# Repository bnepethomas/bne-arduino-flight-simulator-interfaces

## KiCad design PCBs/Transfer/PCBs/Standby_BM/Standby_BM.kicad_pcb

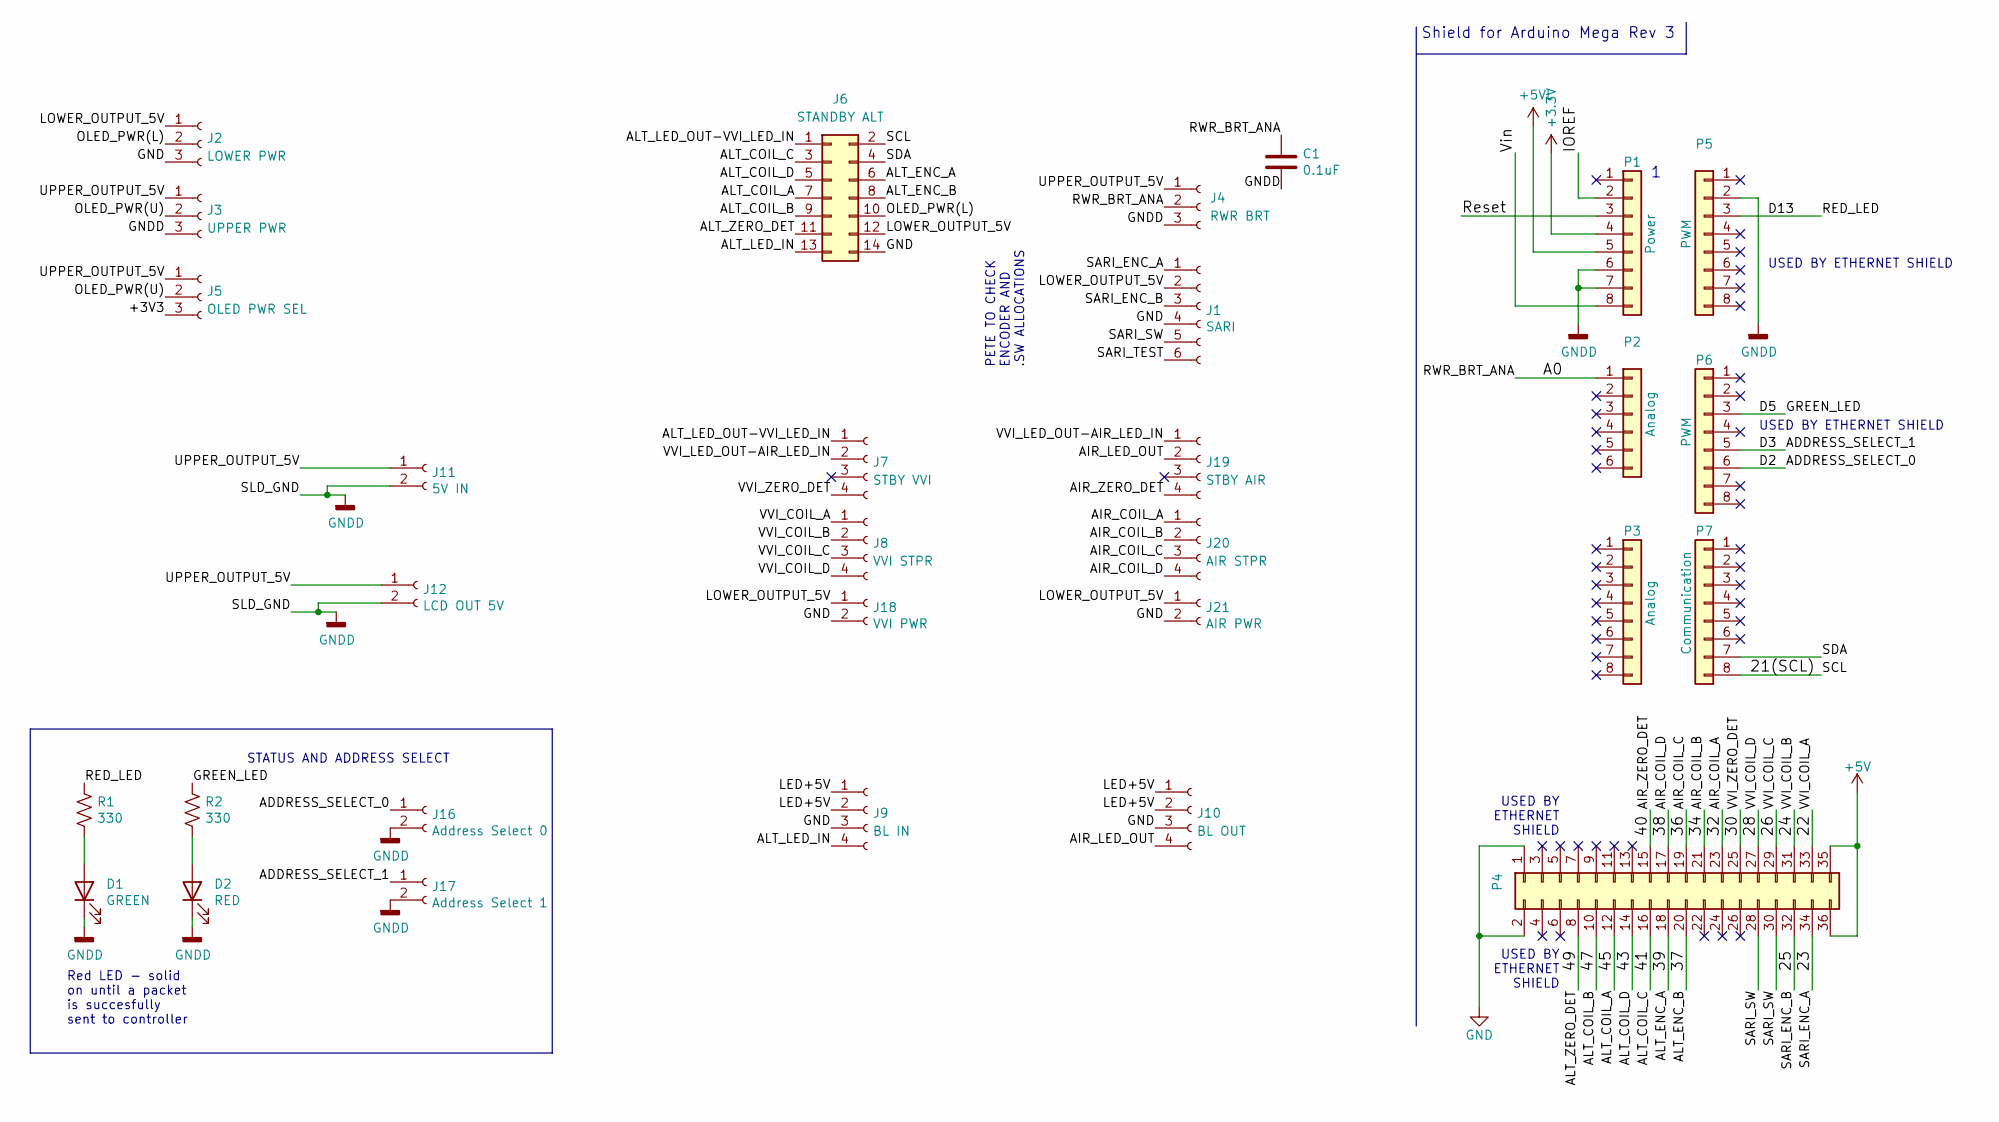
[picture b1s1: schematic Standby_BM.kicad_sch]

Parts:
C1: 0.1uF; C_Disc_D6.0mm_W2.5mm_P5.00mm
D1: GREEN; LED_D3.0mm
D2: RED; LED_D3.0mm
J1: SARI; Molex_KK-254_AE-6410-06A_1x06_P2.54mm_Vertical
J2: LOWER PWR; Molex_KK-254_AE-6410-03A_1x03_P2.54mm_Vertical
J3: UPPER PWR; Molex_KK-254_AE-6410-03A_1x03_P2.54mm_Vertical
J4: RWR BRT; Molex_KK-254_AE-6410-03A_1x03_P2.54mm_Vertical
J5: OLED PWR SEL; PinHeader_1x03_P2.54mm_Vertical
J6: STANDBY ALT; IDC-Header_2x07_P2.54mm_Vertical
J7: STBY VVI; Molex_KK-254_AE-6410-04A_1x04_P2.54mm_Vertical
J8: VVI STPR; Molex_KK-254_AE-6410-04A_1x04_P2.54mm_Vertical
J9: BL IN; Molex_Mini-Fit_Jr_5566-04A_2x02_P4.20mm_Vertical
J10: BL OUT; Molex_Mini-Fit_Jr_5566-04A_2x02_P4.20mm_Vertical
J11: 5V IN; BarrelJack_Horizontal
J12: LCD OUT 5V; BarrelJack_Horizontal
J16: Address Select 0; PinHeader_1x02_P2.54mm_Vertical
J17: Address Select 1; PinHeader_1x02_P2.54mm_Vertical
J18: VVI PWR; Molex_KK-254_AE-6410-02A_1x02_P2.54mm_Vertical
J19: STBY AIR; Molex_KK-254_AE-6410-04A_1x04_P2.54mm_Vertical
J20: AIR STPR; Molex_KK-254_AE-6410-04A_1x04_P2.54mm_Vertical
J21: AIR PWR; Molex_KK-254_AE-6410-02A_1x02_P2.54mm_Vertical
P1: Power; Socket_Strip_Arduino_1x08
P2: Analog; Socket_Strip_Arduino_1x06
P3: Analog; Socket_Strip_Arduino_1x08
P4: Digital; Socket_Strip_Arduino_2x18
P5, P6: PWM; Socket_Strip_Arduino_1x08
P7: Communication; Socket_Strip_Arduino_1x08
R1, R2: 330; PT_R_Axial_DIN0204_L3.6mm_D1.6mm_P2.54mm_Vertical

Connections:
+5V: P4.35, P4.36
+5VL: P1.5
/21(SCL): J6.2, P7.8
/22: J8.1, P4.33
/23: J1.1, P4.34
/24: J8.2, P4.31
/25: J1.3, P4.32
/26: J8.3, P4.29
/28: J8.4, P4.27
/30: J7.4, P4.25
/32: J20.1, P4.23
/34: J20.2, P4.21
/36: J20.3, P4.19
/37: J6.8, P4.20
/38: J20.4, P4.17
/39: J6.6, P4.18
/40: J19.4, P4.15
/41: J6.3, P4.16
/43: J6.5, P4.14
/45: J6.7, P4.12
/47: J6.9, P4.10
/49: J6.11, P4.8
/A0: C1.1, J4.2, P2.1
/A1: P2.2
/A2: P2.3
/A3: P2.4
/A4: P2.5
/A5: P2.6
/ADDRESS_SELECT_0: J16.1, P6.6
/ADDRESS_SELECT_1: J17.1, P6.5
/AIR_LED_OUT: J10.4, J19.2
/ALT_LED_IN: J6.13, J9.4
/ALT_LED_OUT-VVI_LED_IN: J6.1, J7.1
/D5: P6.3, R2.1
/D13: P5.3, R1.1
/IOREF: P1.2
/LED+5V: J9.1, J9.2, J10.1, J10.2
/LOWER_OUTPUT_5V: J1.2, J2.1, J6.12, J18.1, J21.1
/OLED_PWR(L): J2.2, J6.10
/OLED_PWR(U): J3.2, J5.2
/Reset: P1.3
/SARI_SW: J1.5, P4.28, P4.30
/SARI_TEST: J1.6
/SDA: J6.4, P7.7
/UPPER_OUTPUT_5V: J3.1, J4.1, J5.1, J11.1, J12.1
/VVI_LED_OUT-AIR_LED_IN: J7.2, J19.1
/Vin: P1.8
GND: J1.4, J2.3, J6.14, J9.3, J10.3, J18.2, J21.2, P4.1, P4.2
GNDD: C1.2, D1.1 (K), D2.1 (K), J3.3, J4.3, J11.2, J12.2, J16.2, J17.2, P1.6, P1.7, P5.2
unnamed: D1.2 (A), R1.2
unnamed: D2.2 (A), R2.2

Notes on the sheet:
Shield for Arduino Mega Rev 3
USED BY ETHERNET SHIELD
STATUS AND ADDRESS SELECT
USED BY ETHERNET SHIELD
Red LED - solid on until a packet is succesfully sent to controller
PETE TO CHECK ENCODER AND .SW ALLOCATIONS

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
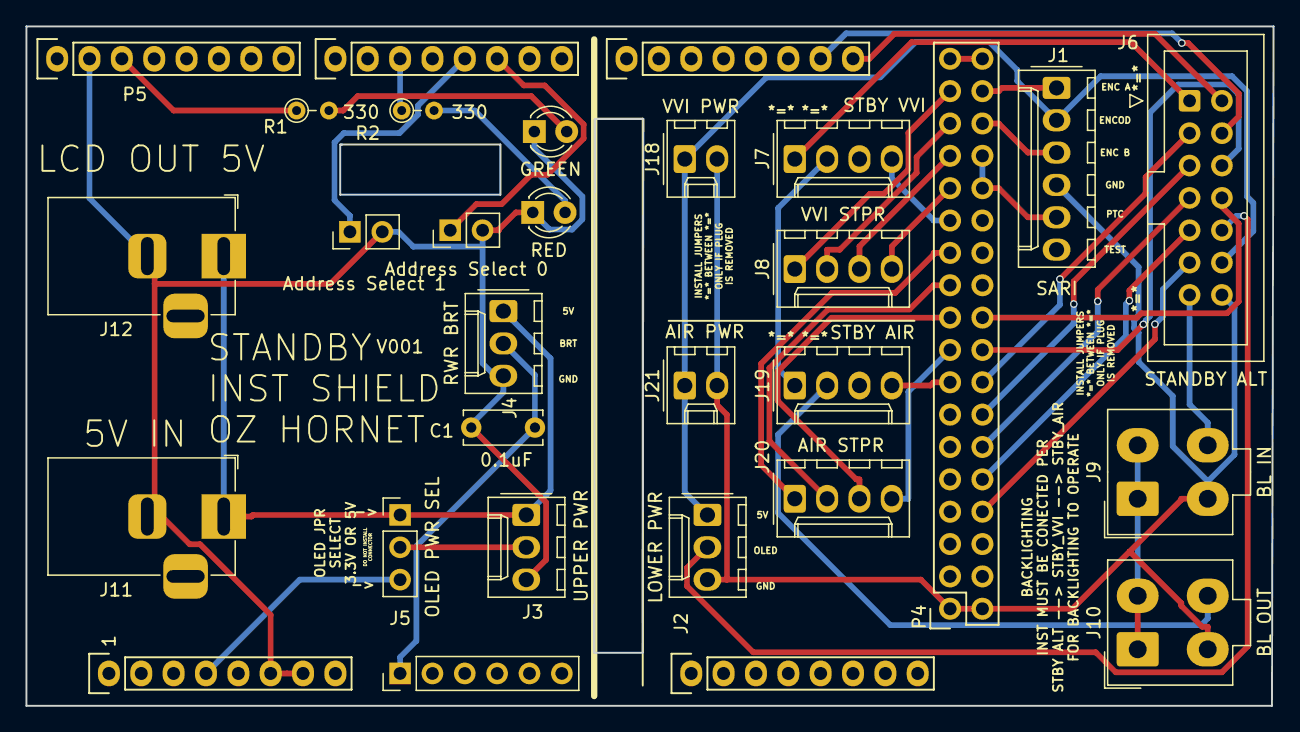
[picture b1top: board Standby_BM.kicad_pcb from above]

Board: 2 copper layers, 97.9 x 53.3 mm, 30 parts (0 on the bottom side), 42 nets.

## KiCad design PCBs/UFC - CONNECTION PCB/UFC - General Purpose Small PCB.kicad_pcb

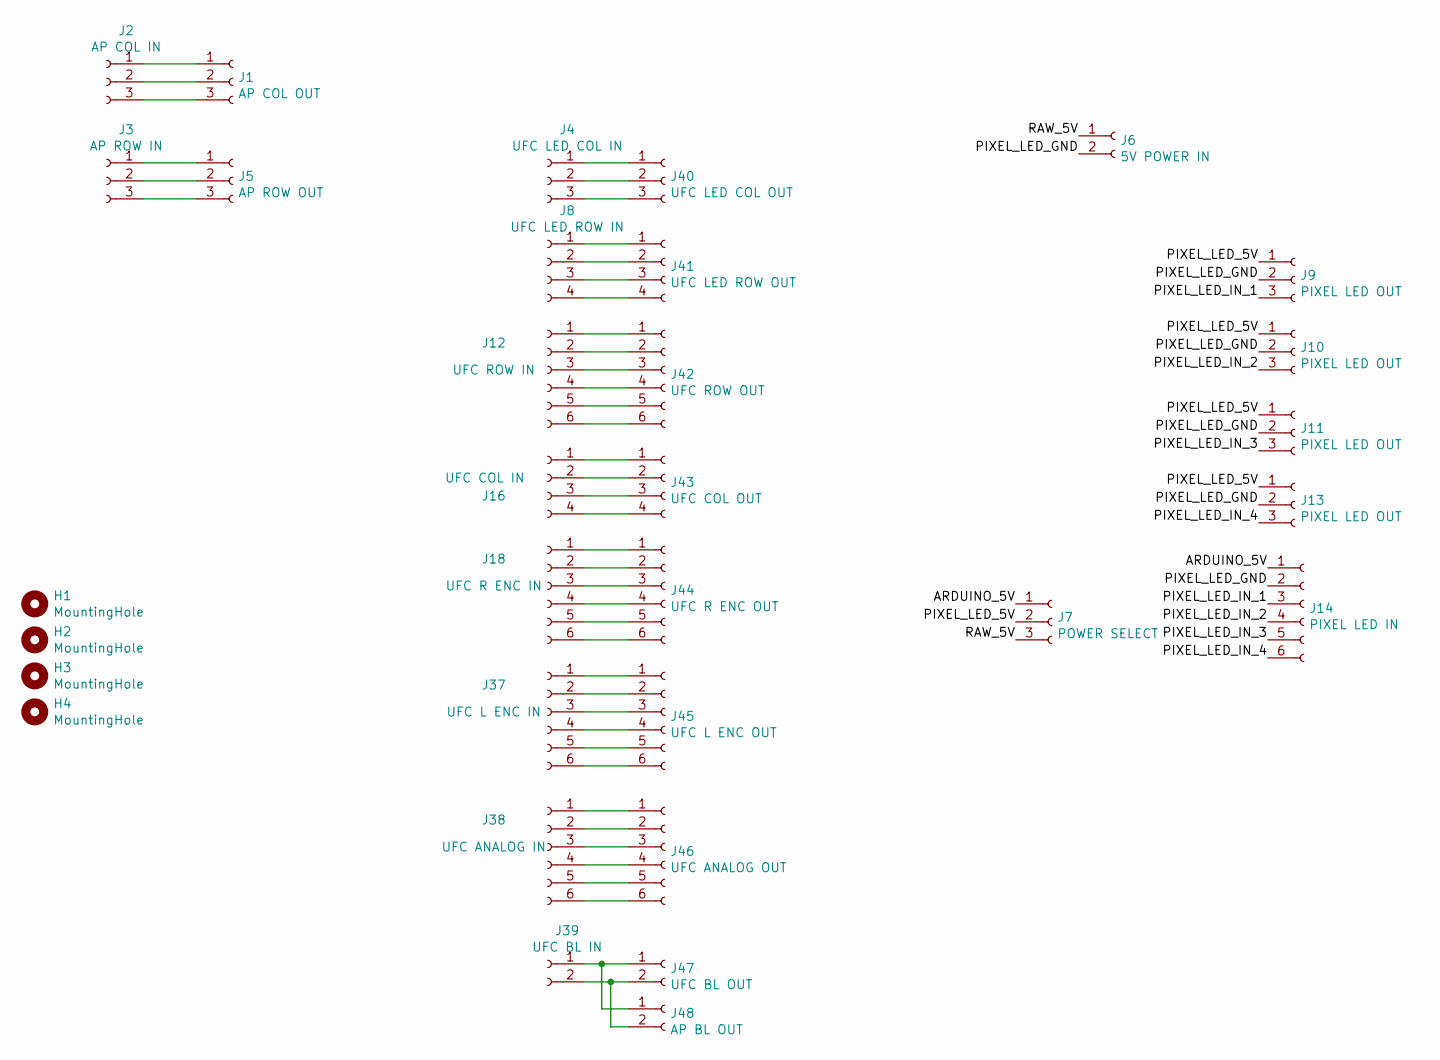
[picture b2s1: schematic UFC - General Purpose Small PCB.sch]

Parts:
H1, H2, H3, H4: MountingHole; MountingHole_3.2mm_M3
J1: AP COL OUT; Molex_1x03_P2.54mm_Vertical
J2: AP COL IN; Molex_1x03_P2.54mm_Vertical
J3: AP ROW IN; Molex_1x03_P2.54mm_Vertical
J4: UFC LED COL IN; Molex_1x03_P2.54mm_Vertical
J5: AP ROW OUT; Molex_1x03_P2.54mm_Vertical
J6: 5V POWER IN; BarrelJack_Horizontal
J7: POWER SELECT; Molex_1x03_P2.54mm_Vertical
J8: UFC LED ROW IN; Molex_1x04_P2.54mm_Vertical
J9, J10, J11, J13: PIXEL LED OUT; Molex_1x03_P2.54mm_Vertical
J12: UFC ROW IN; Molex_1x06_P2.54mm_Vertical
J14: PIXEL LED IN; Molex_1x06_P2.54mm_Vertical
J16: UFC COL IN; Molex_1x04_P2.54mm_Vertical
J18: UFC R ENC IN; Molex_1x06_P2.54mm_Vertical
J37: UFC L ENC IN; Molex_1x06_P2.54mm_Vertical
J38: UFC ANALOG IN; Molex_1x06_P2.54mm_Vertical
J39: UFC BL IN; Molex_1x02_P2.54mm_Vertical
J40: UFC LED COL OUT; Molex_1x03_P2.54mm_Vertical
J41: UFC LED ROW OUT; Molex_1x04_P2.54mm_Vertical
J42: UFC ROW OUT; Molex_1x06_P2.54mm_Vertical
J43: UFC COL OUT; Molex_1x04_P2.54mm_Vertical
J44: UFC R ENC OUT; Molex_1x06_P2.54mm_Vertical
J45: UFC L ENC OUT; Molex_1x06_P2.54mm_Vertical
J46: UFC ANALOG OUT; Molex_1x06_P2.54mm_Vertical
J47: UFC BL OUT; Molex_1x02_P2.54mm_Vertical
J48: AP BL OUT; Molex_1x02_P2.54mm_Vertical

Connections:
/ARDUINO_5V: J7.1, J14.1
/PIXEL_LED_5V: J7.2, J9.1, J10.1, J11.1, J13.1
/PIXEL_LED_GND: J6.2, J9.2, J10.2, J11.2, J13.2, J14.2
/PIXEL_LED_IN_1: J9.3, J14.3
/PIXEL_LED_IN_2: J10.3, J14.4
/PIXEL_LED_IN_3: J11.3, J14.5
/PIXEL_LED_IN_4: J13.3, J14.6
/RAW_5V: J6.1, J7.3
unnamed: J1.1, J2.1
unnamed: J1.2, J2.2
unnamed: J1.3, J2.3
unnamed: J3.1, J5.1
unnamed: J3.2, J5.2
unnamed: J3.3, J5.3
unnamed: J4.1, J40.1
unnamed: J4.2, J40.2
unnamed: J4.3, J40.3
unnamed: J12.1, J42.1
unnamed: J12.2, J42.2
unnamed: J12.3, J42.3
unnamed: J12.4, J42.4
unnamed: J12.5, J42.5
unnamed: J12.6, J42.6
unnamed: J16.1, J43.1
unnamed: J16.2, J43.2
unnamed: J16.3, J43.3
unnamed: J16.4, J43.4
unnamed: J18.1, J44.1
unnamed: J18.2, J44.2
unnamed: J18.3, J44.3
unnamed: J18.4, J44.4
unnamed: J18.5, J44.5
unnamed: J18.6, J44.6
unnamed: J37.1, J45.1
unnamed: J37.2, J45.2
unnamed: J37.3, J45.3
unnamed: J37.4, J45.4
unnamed: J37.5, J45.5
unnamed: J37.6, J45.6
unnamed: J38.1, J46.1
unnamed: J38.2, J46.2
unnamed: J38.3, J46.3
unnamed: J38.4, J46.4
unnamed: J38.5, J46.5
unnamed: J38.6, J46.6
unnamed: J39.1, J47.1, J48.1
unnamed: J39.2, J47.2, J48.2
unnamed: J8.1, J41.1
unnamed: J8.2, J41.2
unnamed: J8.3, J41.3
unnamed: J8.4, J41.4

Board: 2 copper layers, 32 parts (0 on the bottom side), 51 nets, no tracks yet.

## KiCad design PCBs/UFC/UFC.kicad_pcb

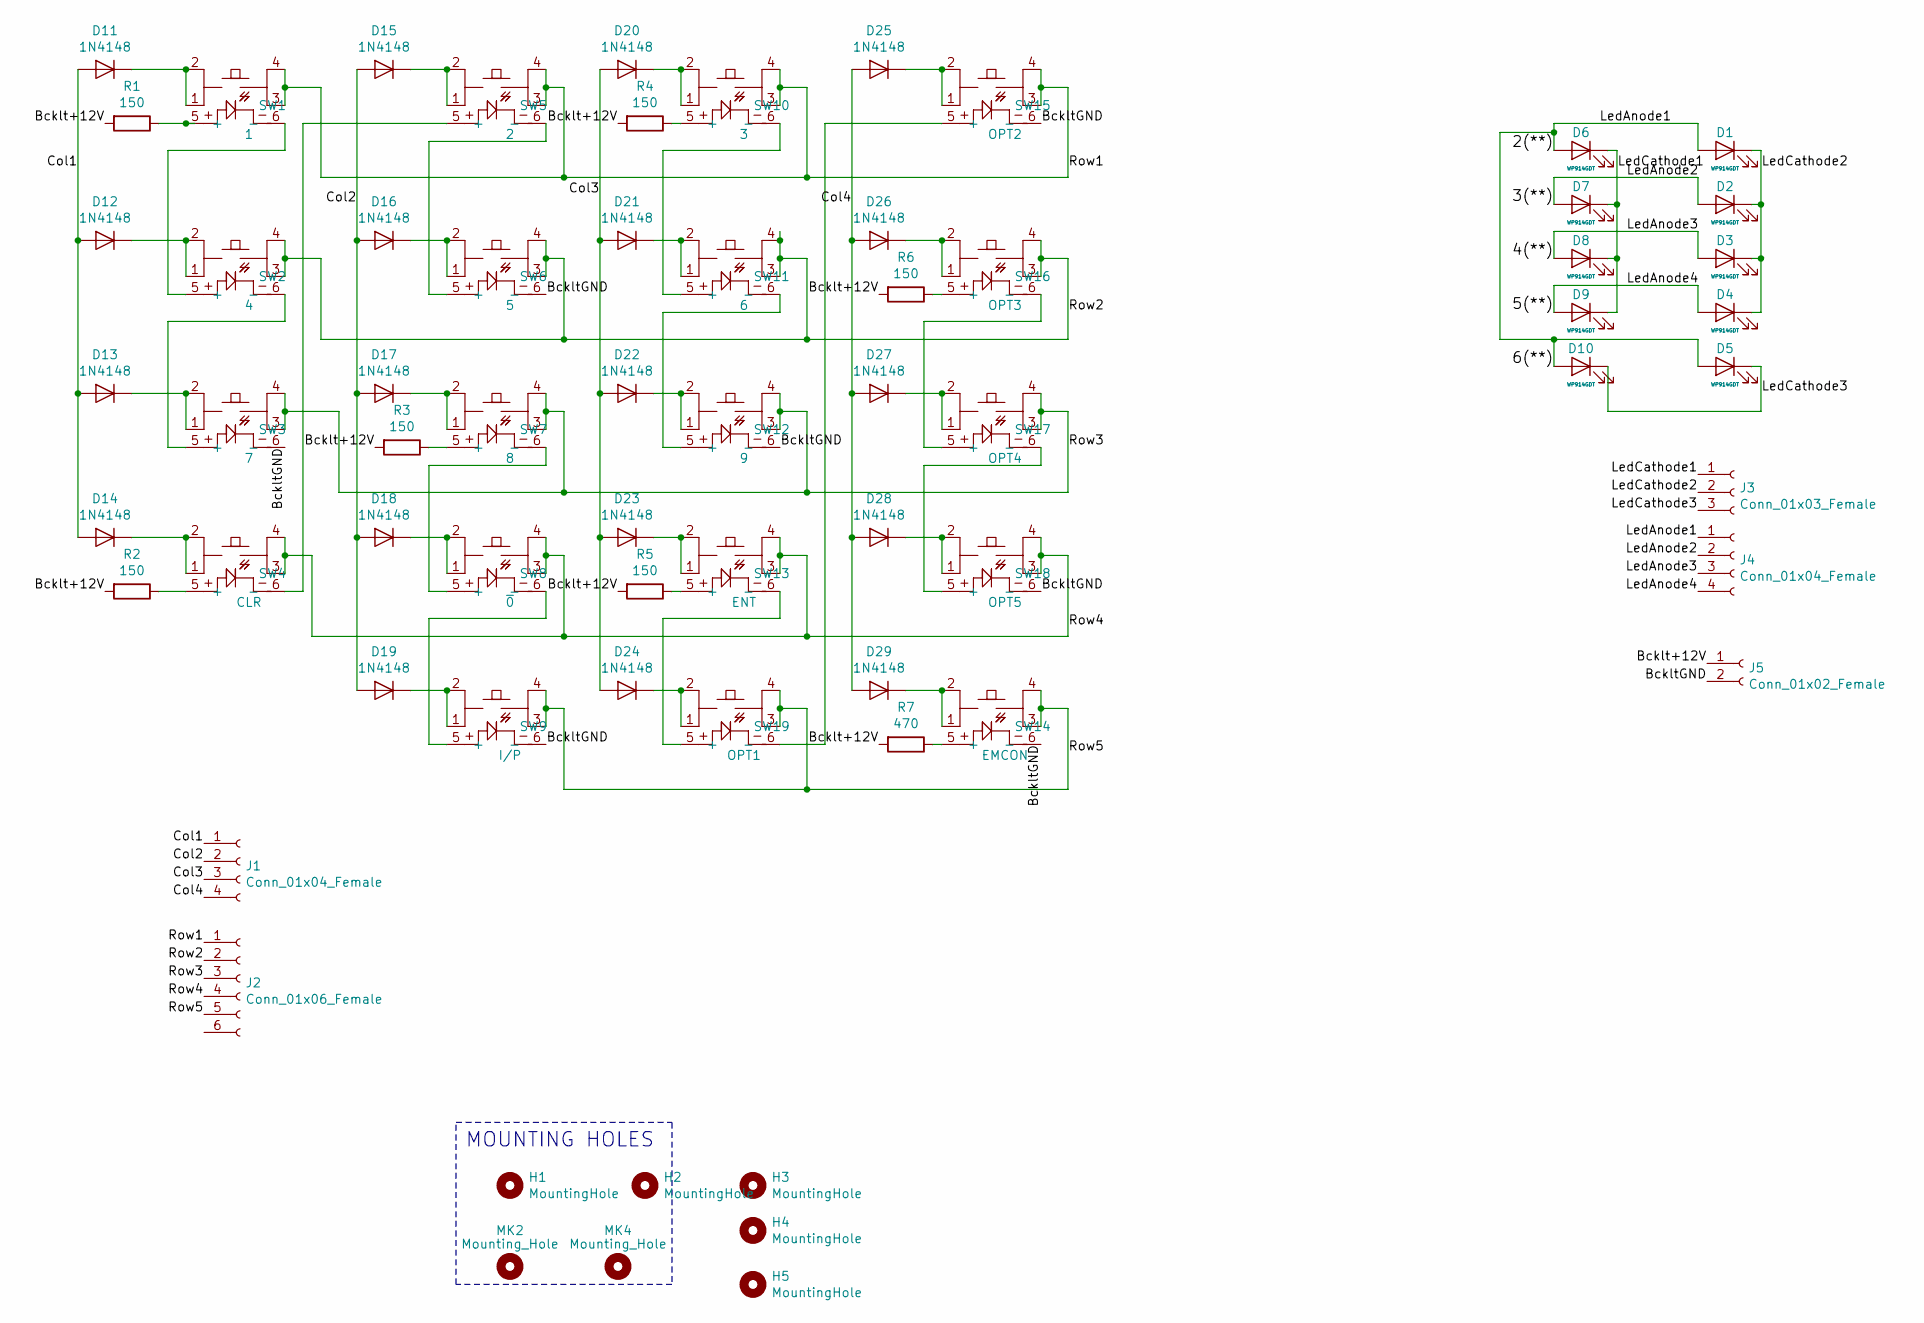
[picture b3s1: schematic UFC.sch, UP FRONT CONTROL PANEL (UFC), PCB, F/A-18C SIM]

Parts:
D1, D2, D3, D4, D5, D6, D7, D8, D9, D10: WP914GDT; LED_D3.0mm
D11, D12, D13, D14, D15, D16, D17, D18, D19, D20, D21, D22, D23, D24, D25, D26, D27, D28, D29: 1N4148; D_DO-35_SOD27_P7.62mm_Horizontal
H1, H2, H3, H4, H5: MountingHole; MountingHole_3.2mm_M3
J1, J4: Conn_01x04_Female; Molex_1x04_P2.54mm_Vertical
J2: Conn_01x06_Female; Molex_1x06_P2.54mm_Vertical
J3: Conn_01x03_Female; Molex_1x03_P2.54mm_Vertical
J5: Conn_01x02_Female; Molex_1x02_P2.54mm_Vertical
MK2, MK4: Mounting_Hole; MountingHole_3mm
R1, R2, R3, R4, R5, R6: 150; R_Axial_DIN0207_L6.3mm_D2.5mm_P7.62mm_Horizontal
R7: 470; R_Axial_DIN0207_L6.3mm_D2.5mm_P7.62mm_Horizontal
SW1: 1; PT_Small_Tactile_Switch_With_LED
SW2: 4; PT_Small_Tactile_Switch_With_LED
SW3: 7; PT_Small_Tactile_Switch_With_LED
SW4: CLR; PT_Small_Tactile_Switch_With_LED
SW5: 2; PT_Small_Tactile_Switch_With_LED
SW6: 5; PT_Small_Tactile_Switch_With_LED
SW7: 8; PT_Small_Tactile_Switch_With_LED
SW8: ~0; PT_Small_Tactile_Switch_With_LED
SW9: I/P; PT_Small_Tactile_Switch_With_LED
SW10: 3; PT_Small_Tactile_Switch_With_LED
SW11: 6; PT_Small_Tactile_Switch_With_LED
SW12: 9; PT_Small_Tactile_Switch_With_LED
SW13: ENT; PT_Small_Tactile_Switch_With_LED
SW14: EMCON; PT_Small_Tactile_Switch_With_LED
SW15: OPT2; PT_Small_Tactile_Switch_With_LED
SW16: OPT3; PT_Small_Tactile_Switch_With_LED
SW17: OPT4; PT_Small_Tactile_Switch_With_LED
SW18: OPT5; PT_Small_Tactile_Switch_With_LED
SW19: OPT1; PT_Small_Tactile_Switch_With_LED

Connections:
/2(**): D1.2 (A), D5.2 (A), D6.2 (A), D10.2 (A), J4.1
/3(**): D2.2 (A), D7.2 (A), J4.2
/4(**): D3.2 (A), D8.2 (A), J4.3
/5(**): D4.2 (A), D9.2 (A), J4.4
/Bcklt+12V: J5.1, R1.2, R2.2, R3.2, R4.2, R5.2, R6.2, R7.2
/BckltGND: J5.2, SW3.6 (-), SW6.6 (-), SW9.6 (-), SW12.6 (-), SW14.6 (-), SW15.6 (-), SW18.6 (-)
/Col1: D11.2 (A), D12.2 (A), D13.2 (A), D14.2 (A), J1.1
/Col2: D15.2 (A), D16.2 (A), D17.2 (A), D18.2 (A), D19.2 (A), J1.2
/Col3: D20.2 (A), D21.2 (A), D22.2 (A), D23.2 (A), D24.2 (A), J1.3
/Col4: D25.2 (A), D26.2 (A), D27.2 (A), D28.2 (A), D29.2 (A), J1.4
/LedCathode1: D6.1 (K), D7.1 (K), D8.1 (K), D9.1 (K), J3.1
/LedCathode2: D1.1 (K), D2.1 (K), D3.1 (K), D4.1 (K), J3.2
/LedCathode3: D5.1 (K), D10.1 (K), J3.3
/Row1: J2.1, SW1.3, SW1.4, SW5.3, SW5.4, SW10.3, SW10.4, SW15.3, SW15.4
/Row2: J2.2, SW2.3, SW2.4, SW6.3, SW6.4, SW11.3, SW11.4, SW16.3, SW16.4
/Row3: J2.3, SW3.3, SW3.4, SW7.3, SW7.4, SW12.3, SW12.4, SW17.3, SW17.4
/Row4: J2.4, SW4.3, SW4.4, SW8.3, SW8.4, SW13.3, SW13.4, SW18.3, SW18.4
/Row5: J2.5, SW9.3, SW9.4, SW14.3, SW14.4, SW19.3, SW19.4
unnamed: D11.1 (K), SW1.1, SW1.2
unnamed: D12.1 (K), SW2.1, SW2.2
unnamed: D13.1 (K), SW3.1, SW3.2
unnamed: D14.1 (K), SW4.1, SW4.2
unnamed: D15.1 (K), SW5.1, SW5.2
unnamed: D16.1 (K), SW6.1, SW6.2
unnamed: D17.1 (K), SW7.1, SW7.2
unnamed: D18.1 (K), SW8.1, SW8.2
unnamed: D19.1 (K), SW9.1, SW9.2
unnamed: D20.1 (K), SW10.1, SW10.2
unnamed: D21.1 (K), SW11.1, SW11.2
unnamed: D22.1 (K), SW12.1, SW12.2
unnamed: D23.1 (K), SW13.1, SW13.2
unnamed: D24.1 (K), SW19.1, SW19.2
unnamed: D25.1 (K), SW15.1, SW15.2
unnamed: D26.1 (K), SW16.1, SW16.2
unnamed: D27.1 (K), SW17.1, SW17.2
unnamed: D28.1 (K), SW18.1, SW18.2
unnamed: D29.1 (K), SW14.1, SW14.2
unnamed: R1.1, SW1.5 (+)
unnamed: R2.1, SW4.5 (+)
unnamed: R3.1, SW7.5 (+)
unnamed: R4.1, SW10.5 (+)
unnamed: R5.1, SW13.5 (+)
unnamed: R6.1, SW16.5 (+)
unnamed: R7.1, SW14.5 (+)
unnamed: SW1.6 (-), SW2.5 (+)
unnamed: SW2.6 (-), SW3.5 (+)
unnamed: SW4.6 (-), SW5.5 (+)
unnamed: SW5.6 (-), SW6.5 (+)
unnamed: SW7.6 (-), SW8.5 (+)
unnamed: SW8.6 (-), SW9.5 (+)
unnamed: SW10.6 (-), SW11.5 (+)
unnamed: SW11.6 (-), SW12.5 (+)
unnamed: SW13.6 (-), SW19.5 (+)
unnamed: SW15.5 (+), SW19.6 (-)
unnamed: SW16.6 (-), SW17.5 (+)
unnamed: SW17.6 (-), SW18.5 (+)

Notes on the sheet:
MOUNTING HOLES

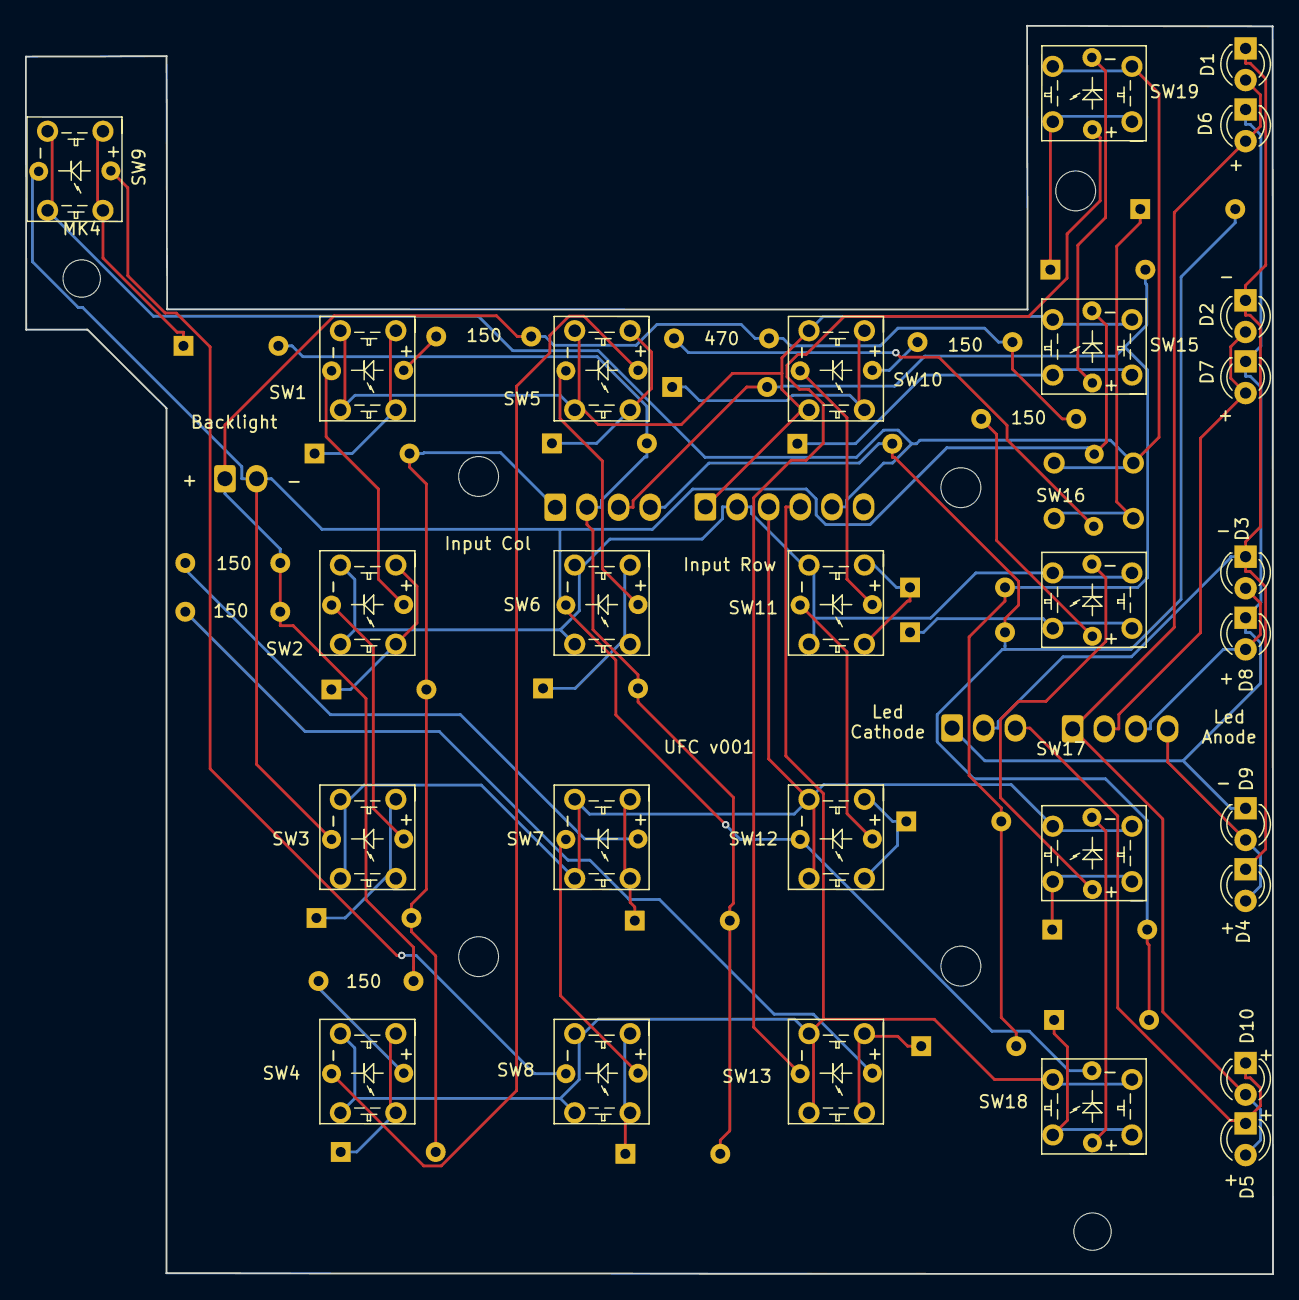
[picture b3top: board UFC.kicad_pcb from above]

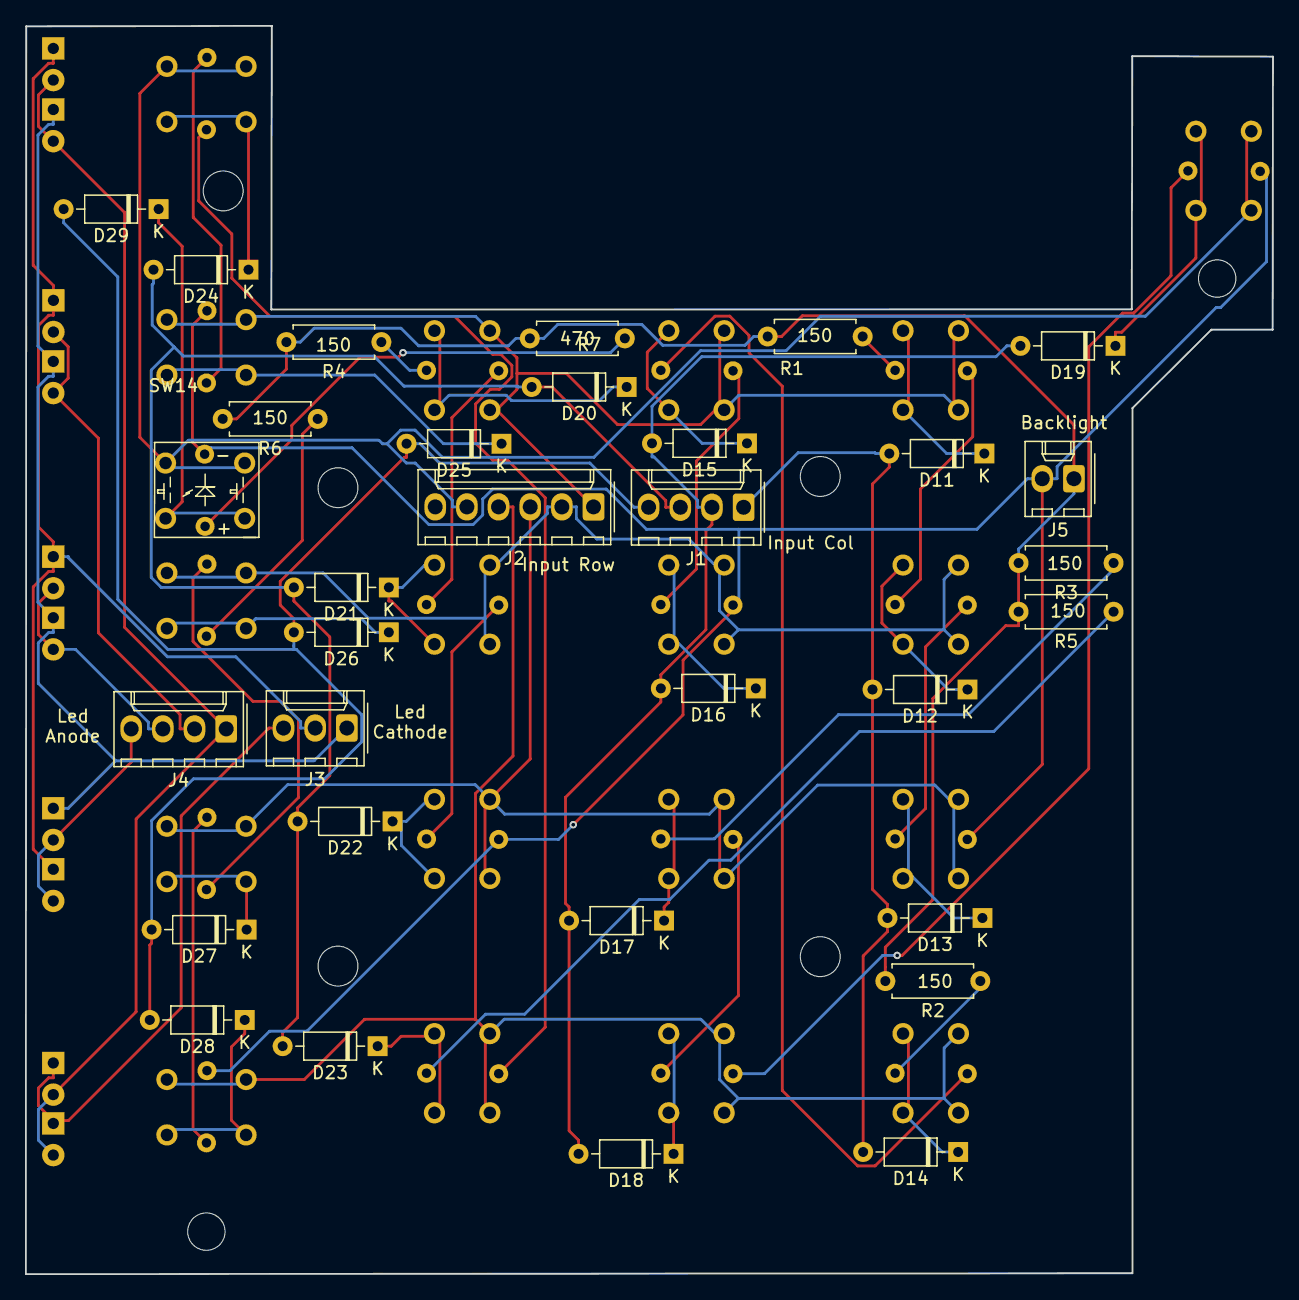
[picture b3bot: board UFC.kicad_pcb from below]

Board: 2 copper layers, 100.0 x 100.1 mm, 67 parts (32 on the bottom side), 56 nets.

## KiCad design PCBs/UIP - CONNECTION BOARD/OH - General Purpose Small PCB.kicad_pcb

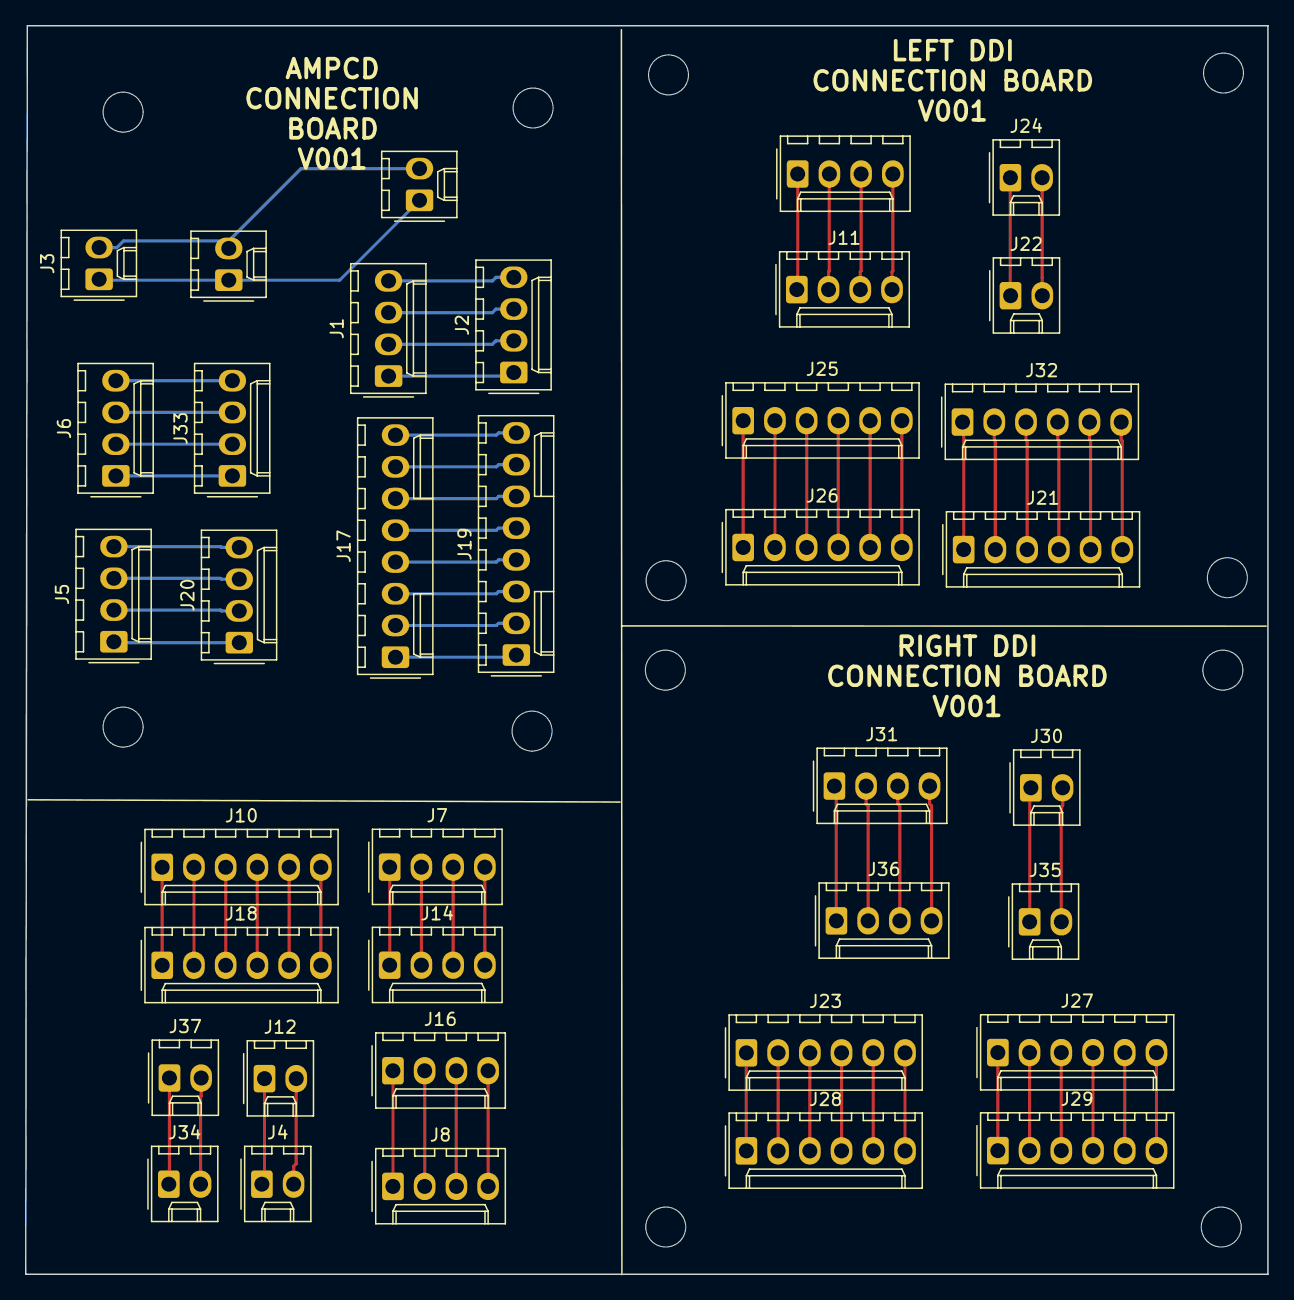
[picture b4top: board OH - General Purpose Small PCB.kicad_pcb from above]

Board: 2 copper layers, 99.4 x 99.9 mm, 49 parts (0 on the bottom side), 76 nets.

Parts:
H1, H2, H3, H4, H9, H10, H11, H12, H13, H14, H15, H16: MountingHole; MountingHole_3.2mm_M3
J1: AMPCD COL IN; Molex_1x04_P2.54mm_Vertical
J2: AMPCD COL OUT; Molex_1x04_P2.54mm_Vertical
J3: H/C BL OUT; Molex_1x02_P2.54mm_Vertical
J4, J12, J34, J37: SPARE; Molex_1x02_P2.54mm_Vertical
J5: AMPCD CRS IN; Molex_1x04_P2.54mm_Vertical
J6: AMPCD HDG IN; Molex_1x04_P2.54mm_Vertical
J7, J8, J14, J16: SPARE; Molex_1x04_P2.54mm_Vertical
J9: AMPCD BL IN; Molex_1x02_P2.54mm_Vertical
J10, J18: SPARE; Molex_1x06_P2.54mm_Vertical
J11: L DDI ANLOG IN; Molex_1x04_P2.54mm_Vertical
J13: AMPCD BL OUT; Molex_1x02_P2.54mm_Vertical
J15: L DDI ANLOG OUT; Molex_1x04_P2.54mm_Vertical
J17: AMPCD ROW IN; Molex_1x08_P2.54mm_Vertical
J19: AMPCD ROW OUT; Molex_1x08_P2.54mm_Vertical
J20: AMPCD CRS OUT; Molex_1x04_P2.54mm_Vertical
J21, J26: L DDI ROW IN; Molex_1x06_P2.54mm_Vertical
J22: L DDI BL IN; Molex_1x02_P2.54mm_Vertical
J23, J27: R DDI ROW IN; Molex_1x06_P2.54mm_Vertical
J24: L DDI BL OUT; Molex_1x02_P2.54mm_Vertical
J25: L DDI ROW OUT; Molex_1x06_P2.54mm_Vertical
J28: R DDI ROW OUT; Molex_1x06_P2.54mm_Vertical
J29: R DDI COL OUT; Molex_1x06_P2.54mm_Vertical
J30: R DDI BL IN; Molex_1x02_P2.54mm_Vertical
J31: R DDI ANLOG IN; Molex_1x04_P2.54mm_Vertical
J32: L DDI COL OUT; Molex_1x06_P2.54mm_Vertical
J33: AMPCD HDG OUT; Molex_1x04_P2.54mm_Vertical
J35: R DDI BL OUT; Molex_1x02_P2.54mm_Vertical
J36: R DDI ANLOG OUT; Molex_1x04_P2.54mm_Vertical

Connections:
unnamed: J1.1, J2.1
unnamed: J1.2, J2.2
unnamed: J1.3, J2.3
unnamed: J1.4, J2.4
unnamed: J10.1, J18.1
unnamed: J10.2, J18.2
unnamed: J10.3, J18.3
unnamed: J10.4, J18.4
unnamed: J10.5, J18.5
unnamed: J10.6, J18.6
unnamed: J11.1, J15.1
unnamed: J11.2, J15.2
unnamed: J11.3, J15.3
unnamed: J11.4, J15.4
unnamed: J4.1, J12.1
unnamed: J4.2, J12.2
unnamed: J3.1, J9.1, J13.1
unnamed: J3.2, J9.2, J13.2
unnamed: J7.1, J14.1
unnamed: J7.2, J14.2
unnamed: J7.3, J14.3
unnamed: J7.4, J14.4
unnamed: J8.1, J16.1
unnamed: J8.2, J16.2
unnamed: J8.3, J16.3
unnamed: J8.4, J16.4
unnamed: J17.1, J19.1
unnamed: J17.2, J19.2
unnamed: J17.3, J19.3
unnamed: J17.4, J19.4
unnamed: J17.5, J19.5
unnamed: J17.6, J19.6
unnamed: J17.7, J19.7
unnamed: J17.8, J19.8
unnamed: J5.1, J20.1
unnamed: J5.2, J20.2
unnamed: J5.3, J20.3
unnamed: J5.4, J20.4
unnamed: J21.1, J32.1
unnamed: J21.2, J32.2
unnamed: J21.3, J32.3
unnamed: J21.4, J32.4
unnamed: J21.5, J32.5
unnamed: J21.6, J32.6
unnamed: J22.1, J24.1
unnamed: J22.2, J24.2
unnamed: J23.1, J28.1
unnamed: J23.2, J28.2
unnamed: J23.3, J28.3
unnamed: J23.4, J28.4
unnamed: J23.5, J28.5
unnamed: J23.6, J28.6
unnamed: J25.1, J26.1
unnamed: J25.2, J26.2
unnamed: J25.3, J26.3
unnamed: J25.4, J26.4
unnamed: J25.5, J26.5
unnamed: J25.6, J26.6
unnamed: J27.1, J29.1
unnamed: J27.2, J29.2
unnamed: J27.3, J29.3
unnamed: J27.4, J29.4
unnamed: J27.5, J29.5
unnamed: J27.6, J29.6
unnamed: J30.1, J35.1
unnamed: J30.2, J35.2
unnamed: J31.1, J36.1
unnamed: J31.2, J36.2
unnamed: J31.3, J36.3
unnamed: J31.4, J36.4
unnamed: J6.1, J33.1
unnamed: J6.2, J33.2
unnamed: J6.3, J33.3
unnamed: J6.4, J33.4
unnamed: J34.1, J37.1
unnamed: J34.2, J37.2
